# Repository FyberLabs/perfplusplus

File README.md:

# perfplusplus
# Shields and capes that are inspired by https://www.crowdsupply.com/ben-wang/perf-2

Arduino Uno:

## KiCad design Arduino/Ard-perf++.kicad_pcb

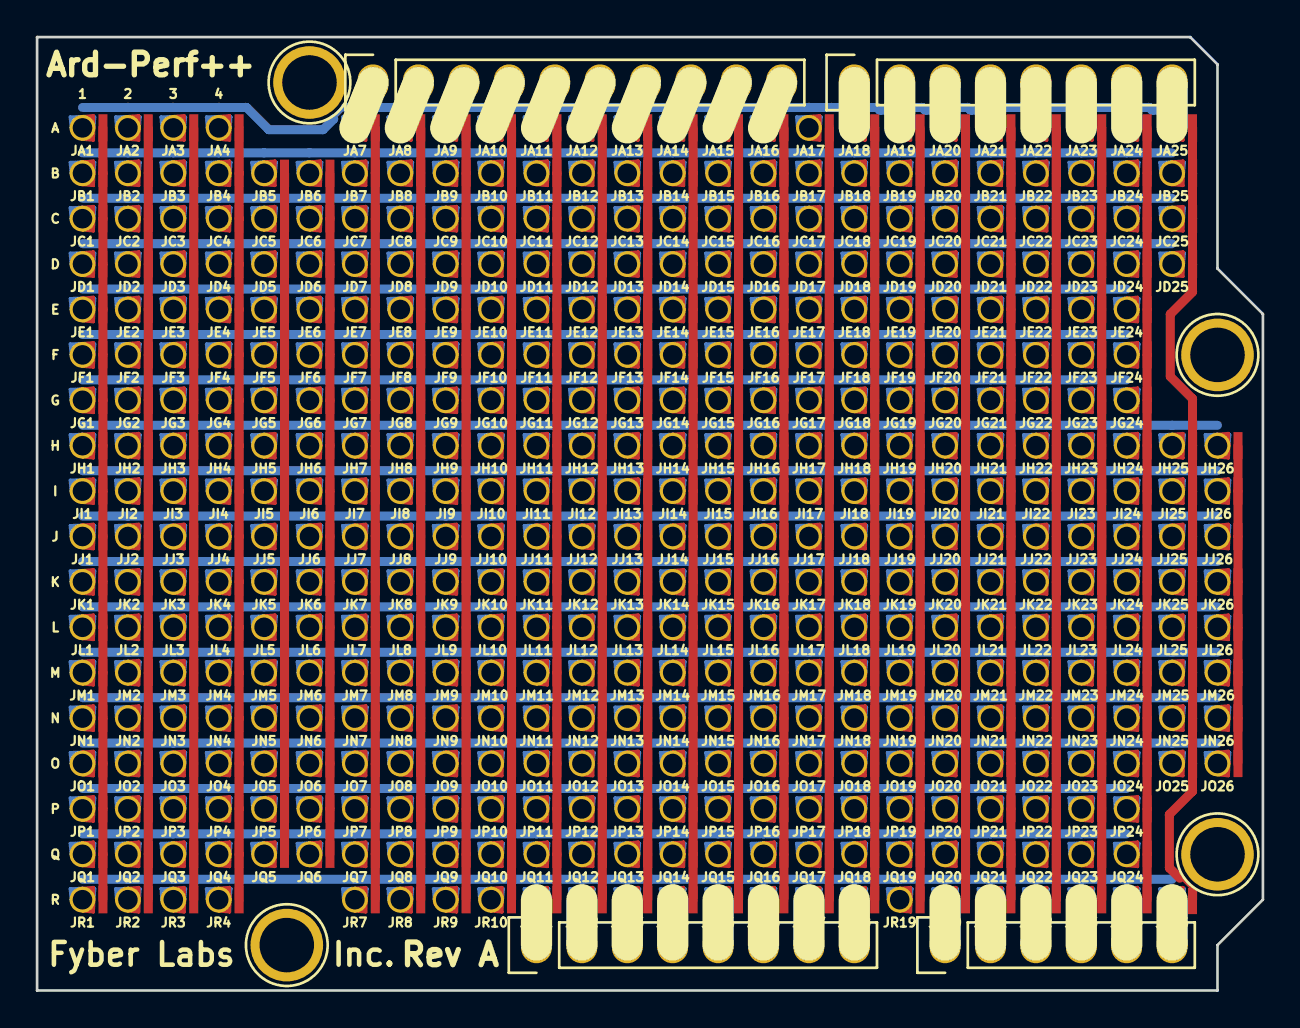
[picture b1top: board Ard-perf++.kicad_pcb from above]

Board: 2 copper layers, 68.6 x 53.3 mm, 457 parts (0 on the bottom side), 76 nets.

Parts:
JA1, JA2, JA3, JA4, JA7, JA8, JA9, JA10, JA11, JA12, JA13, JA14, JA15, JA16, JA17, JA18, JA19, JA20, JA21, JA22, JA23, JA24, JA25: perf+2; 2.54D
JB1, JB2, JB3, JB4, JB5, JB6, JB7, JB8, JB9, JB10, JB11, JB12, JB13, JB14, JB15, JB16, JB17, JB18, JB19, JB20, JB21, JB22, JB23, JB24, JB25: perf+2; 2.54D
JC1, JC2, JC3, JC4, JC5, JC6, JC7, JC8, JC9, JC10, JC11, JC12, JC13, JC14, JC15, JC16, JC17, JC18, JC19, JC20, JC21, JC22, JC23, JC24, JC25: perf+2; 2.54D
JD1, JD2, JD3, JD4, JD5, JD6, JD7, JD8, JD9, JD10, JD11, JD12, JD13, JD14, JD15, JD16, JD17, JD18, JD19, JD20, JD21, JD22, JD23, JD24, JD25: perf+2; 2.54D
JE1, JE2, JE3, JE4, JE5, JE6, JE7, JE8, JE9, JE10, JE11, JE12, JE13, JE14, JE15, JE16, JE17, JE18, JE19, JE20, JE21, JE22, JE23, JE24: perf+2; 2.54D
JF1, JF2, JF3, JF4, JF5, JF6, JF7, JF8, JF9, JF10, JF11, JF12, JF13, JF14, JF15, JF16, JF17, JF18, JF19, JF20, JF21, JF22, JF23, JF24: perf+2; 2.54D
JG1, JG2, JG3, JG4, JG5, JG6, JG7, JG8, JG9, JG10, JG11, JG12, JG13, JG14, JG15, JG16, JG17, JG18, JG19, JG20, JG21, JG22, JG23, JG24: perf+2; 2.54D
JH1, JH2, JH3, JH4, JH5, JH6, JH7, JH8, JH9, JH10, JH11, JH12, JH13, JH14, JH15, JH16, JH17, JH18, JH19, JH20, JH21, JH22, JH23, JH24, JH25, JH26: perf+2; 2.54D
JI1, JI2, JI3, JI4, JI5, JI6, JI7, JI8, JI9, JI10, JI11, JI12, JI13, JI14, JI15, JI16, JI17, JI18, JI19, JI20, JI21, JI22, JI23, JI24, JI25, JI26: perf+2; 2.54D
JJ1, JJ2, JJ3, JJ4, JJ5, JJ6, JJ7, JJ8, JJ9, JJ10, JJ11, JJ12, JJ13, JJ14, JJ15, JJ16, JJ17, JJ18, JJ19, JJ20, JJ21, JJ22, JJ23, JJ24, JJ25, JJ26: perf+2; 2.54D
JK1, JK2, JK3, JK4, JK5, JK6, JK7, JK8, JK9, JK10, JK11, JK12, JK13, JK14, JK15, JK16, JK17, JK18, JK19, JK20, JK21, JK22, JK23, JK24, JK25, JK26: perf+2; 2.54D
JL1, JL2, JL3, JL4, JL5, JL6, JL7, JL8, JL9, JL10, JL11, JL12, JL13, JL14, JL15, JL16, JL17, JL18, JL19, JL20, JL21, JL22, JL23, JL24, JL25, JL26: perf+2; 2.54D
JM1, JM2, JM3, JM4, JM5, JM6, JM7, JM8, JM9, JM10, JM11, JM12, JM13, JM14, JM15, JM16, JM17, JM18, JM19, JM20, JM21, JM22, JM23, JM24, JM25, JM26: perf+2; 2.54D
JN1, JN2, JN3, JN4, JN5, JN6, JN7, JN8, JN9, JN10, JN11, JN12, JN13, JN14, JN15, JN16, JN17, JN18, JN19, JN20, JN21, JN22, JN23, JN24, JN25, JN26: perf+2; 2.54D
JO1, JO2, JO3, JO4, JO5, JO6, JO7, JO8, JO9, JO10, JO11, JO12, JO13, JO14, JO15, JO16, JO17, JO18, JO19, JO20, JO21, JO22, JO23, JO24, JO25, JO26: perf+2; 2.54D
JP1, JP2, JP3, JP4, JP5, JP6, JP7, JP8, JP9, JP10, JP11, JP12, JP13, JP14, JP15, JP16, JP17, JP18, JP19, JP20, JP21, JP22, JP23, JP24: perf+2; 2.54D
JQ1, JQ2, JQ3, JQ4, JQ5, JQ6, JQ7, JQ8, JQ9, JQ10, JQ11, JQ12, JQ13, JQ14, JQ15, JQ16, JQ17, JQ18, JQ19, JQ20, JQ21, JQ22, JQ23, JQ24: perf+2; 2.54D
JR1, JR2, JR3, JR4, JR7, JR8, JR9, JR10, JR11, JR12, JR13, JR14, JR15, JR16, JR17, JR18, JR19, JR20, JR21, JR22, JR23, JR24, JR25: perf+2; 2.54D
P1: Power; Socket_Strip_Arduino_1x08
P2: Analog; Socket_Strip_Arduino_1x06
P3: Digital; Socket_Strip_Arduino_1x10
P4: Digital; Socket_Strip_Arduino_1x08
P5, P6, P7, P8: CONN_01X01; Arduino_1pin

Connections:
+3V3: JR14.1, P1.4
+5V: JR15.1, P1.5
/15x25perf2/JK: JK1.3, JK2.3, JK3.3, JK4.3, JK5.3, JK6.3, JK7.3, JK8.3, JK9.3, JK10.3, JK11.3, JK12.3, JK13.3, JK14.3, JK15.3, JK16.3, JK17.3, JK18.3, JK19.3, JK20.3, JK21.3, JK22.3, JK23.3, JK24.3, JK25.3, JK26.3
/15x25perf2/JL: JL1.3, JL2.3, JL3.3, JL4.3, JL5.3, JL6.3, JL7.3, JL8.3, JL9.3, JL10.3, JL11.3, JL12.3, JL13.3, JL14.3, JL15.3, JL16.3, JL17.3, JL18.3, JL19.3, JL20.3, JL21.3, JL22.3, JL23.3, JL24.3, JL25.3, JL26.3
/15x25perf2/JM: JM1.3, JM2.3, JM3.3, JM4.3, JM5.3, JM6.3, JM7.3, JM8.3, JM9.3, JM10.3, JM11.3, JM12.3, JM13.3, JM14.3, JM15.3, JM16.3, JM17.3, JM18.3, JM19.3, JM20.3, JM21.3, JM22.3, JM23.3, JM24.3, JM25.3, JM26.3
/15x25perf2/JN: JN1.3, JN2.3, JN3.3, JN4.3, JN5.3, JN6.3, JN7.3, JN8.3, JN9.3, JN10.3, JN11.3, JN12.3, JN13.3, JN14.3, JN15.3, JN16.3, JN17.3, JN18.3, JN19.3, JN20.3, JN21.3, JN22.3, JN23.3, JN24.3, JN25.3, JN26.3
/15x25perf2/JO: JO1.3, JO2.3, JO3.3, JO4.3, JO5.3, JO6.3, JO7.3, JO8.3, JO9.3, JO10.3, JO11.3, JO12.3, JO13.3, JO14.3, JO15.3, JO16.3, JO17.3, JO18.3, JO19.3, JO20.3, JO21.3, JO22.3, JO23.3, JO24.3, JO25.3, JO26.3
/15x25perf2/JP: JP1.3, JP2.3, JP3.3, JP4.3, JP5.3, JP6.3, JP7.3, JP8.3, JP9.3, JP10.3, JP11.3, JP12.3, JP13.3, JP14.3, JP15.3, JP16.3, JP17.3, JP18.3, JP19.3, JP20.3, JP21.3, JP22.3, JP23.3, JP24.3
/15x25perf2/JQ: JQ1.3, JQ2.3, JQ3.3, JQ4.3, JQ5.3, JQ6.3, JQ7.3, JQ8.3, JQ9.3, JQ10.3, JQ11.3, JQ12.3, JQ13.3, JQ14.3, JQ15.3, JQ16.3, JQ17.3, JQ18.3, JQ19.3, JQ20.3, JQ21.3, JQ22.3, JQ23.3, JQ24.3
/15x25perf2/JR: JR1.3, JR2.3, JR3.3, JR4.3, JR7.3, JR8.3, JR9.3, JR10.3, JR11.3, JR12.3, JR13.3, JR14.3, JR15.3, JR16.3, JR17.3, JR18.3, JR19.3, JR20.3, JR21.3, JR22.3, JR23.3, JR24.3, JR25.3
/15x25perf2/JR11: JR11.1, P1.1
/15x25perf2/JR12: JR12.1, P1.2
/15x25perf2/JR13: JR13.1, P1.3
/15x25perf2/JR16: JR16.1, P1.6
/15x25perf2/JR17: JR17.1, P1.7
/15x25perf2/JR18: JR18.1, P1.8
/15x25perf2/JR20: JR20.1, P2.1
/15x25perf2/JR21: JR21.1, P2.2
/15x25perf2/JR22: JR22.1, P2.3
/15x25perf2/JR23: JR23.1, P2.4
/15x25perf2/JR24: JR24.1, P2.5
/15x25perf2/JR25: JR25.1, P2.6
/15x25perf/J1: JA1.2, JB1.2, JC1.2, JD1.2, JE1.2, JF1.2, JG1.2, JH1.2, JI1.2, JJ1.2, JK1.2, JL1.2, JM1.2, JN1.2, JO1.2, JP1.2, JQ1.2, JR1.2
/15x25perf/J2: JA2.2, JB2.2, JC2.2, JD2.2, JE2.2, JF2.2, JG2.2, JH2.2, JI2.2, JJ2.2, JK2.2, JL2.2, JM2.2, JN2.2, JO2.2, JP2.2, JQ2.2, JR2.2
/15x25perf/J3: JA3.2, JB3.2, JC3.2, JD3.2, JE3.2, JF3.2, JG3.2, JH3.2, JI3.2, JJ3.2, JK3.2, JL3.2, JM3.2, JN3.2, JO3.2, JP3.2, JQ3.2, JR3.2
/15x25perf/J4: JA4.2, JB4.2, JC4.2, JD4.2, JE4.2, JF4.2, JG4.2, JH4.2, JI4.2, JJ4.2, JK4.2, JL4.2, JM4.2, JN4.2, JO4.2, JP4.2, JQ4.2, JR4.2
/15x25perf/J5: JB5.2, JC5.2, JD5.2, JE5.2, JF5.2, JG5.2, JH5.2, JI5.2, JJ5.2, JK5.2, JL5.2, JM5.2, JN5.2, JO5.2, JP5.2, JQ5.2
/15x25perf/J6: JB6.2, JC6.2, JD6.2, JE6.2, JF6.2, JG6.2, JH6.2, JI6.2, JJ6.2, JK6.2, JL6.2, JM6.2, JN6.2, JO6.2, JP6.2, JQ6.2
/15x25perf/J7: JA7.2, JB7.2, JC7.2, JD7.2, JE7.2, JF7.2, JG7.2, JH7.2, JI7.2, JJ7.2, JK7.2, JL7.2, JM7.2, JN7.2, JO7.2, JP7.2, JQ7.2, JR7.2
/15x25perf/J8: JA8.2, JB8.2, JC8.2, JD8.2, JE8.2, JF8.2, JG8.2, JH8.2, JI8.2, JJ8.2, JK8.2, JL8.2, JM8.2, JN8.2, JO8.2, JP8.2, JQ8.2, JR8.2
/15x25perf/J9: JA9.2, JB9.2, JC9.2, JD9.2, JE9.2, JF9.2, JG9.2, JH9.2, JI9.2, JJ9.2, JK9.2, JL9.2, JM9.2, JN9.2, JO9.2, JP9.2, JQ9.2, JR9.2
/15x25perf/J10: JA10.2, JB10.2, JC10.2, JD10.2, JE10.2, JF10.2, JG10.2, JH10.2, JI10.2, JJ10.2, JK10.2, JL10.2, JM10.2, JN10.2, JO10.2, JP10.2, JQ10.2, JR10.2
/15x25perf/J11: JA11.2, JB11.2, JC11.2, JD11.2, JE11.2, JF11.2, JG11.2, JH11.2, JI11.2, JJ11.2, JK11.2, JL11.2, JM11.2, JN11.2, JO11.2, JP11.2, JQ11.2, JR11.2
/15x25perf/J12: JA12.2, JB12.2, JC12.2, JD12.2, JE12.2, JF12.2, JG12.2, JH12.2, JI12.2, JJ12.2, JK12.2, JL12.2, JM12.2, JN12.2, JO12.2, JP12.2, JQ12.2, JR12.2
/15x25perf/J13: JA13.2, JB13.2, JC13.2, JD13.2, JE13.2, JF13.2, JG13.2, JH13.2, JI13.2, JJ13.2, JK13.2, JL13.2, JM13.2, JN13.2, JO13.2, JP13.2, JQ13.2, JR13.2
/15x25perf/J14: JA14.2, JB14.2, JC14.2, JD14.2, JE14.2, JF14.2, JG14.2, JH14.2, JI14.2, JJ14.2, JK14.2, JL14.2, JM14.2, JN14.2, JO14.2, JP14.2, JQ14.2, JR14.2
/15x25perf/J15: JA15.2, JB15.2, JC15.2, JD15.2, JE15.2, JF15.2, JG15.2, JH15.2, JI15.2, JJ15.2, JK15.2, JL15.2, JM15.2, JN15.2, JO15.2, JP15.2, JQ15.2, JR15.2
/15x25perf/J16: JA16.2, JB16.2, JC16.2, JD16.2, JE16.2, JF16.2, JG16.2, JH16.2, JI16.2, JJ16.2, JK16.2, JL16.2, JM16.2, JN16.2, JO16.2, JP16.2, JQ16.2, JR16.2
/15x25perf/J17: JA17.2, JB17.2, JC17.2, JD17.2, JE17.2, JF17.2, JG17.2, JH17.2, JI17.2, JJ17.2, JK17.2, JL17.2, JM17.2, JN17.2, JO17.2, JP17.2, JQ17.2, JR17.2
/15x25perf/J18: JA18.2, JB18.2, JC18.2, JD18.2, JE18.2, JF18.2, JG18.2, JH18.2, JI18.2, JJ18.2, JK18.2, JL18.2, JM18.2, JN18.2, JO18.2, JP18.2, JQ18.2, JR18.2
/15x25perf/J19: JA19.2, JB19.2, JC19.2, JD19.2, JE19.2, JF19.2, JG19.2, JH19.2, JI19.2, JJ19.2, JK19.2, JL19.2, JM19.2, JN19.2, JO19.2, JP19.2, JQ19.2, JR19.2
/15x25perf/J20: JA20.2, JB20.2, JC20.2, JD20.2, JE20.2, JF20.2, JG20.2, JH20.2, JI20.2, JJ20.2, JK20.2, JL20.2, JM20.2, JN20.2, JO20.2, JP20.2, JQ20.2, JR20.2
/15x25perf/J21: JA21.2, JB21.2, JC21.2, JD21.2, JE21.2, JF21.2, JG21.2, JH21.2, JI21.2, JJ21.2, JK21.2, JL21.2, JM21.2, JN21.2, JO21.2, JP21.2, JQ21.2, JR21.2
/15x25perf/J22: JA22.2, JB22.2, JC22.2, JD22.2, JE22.2, JF22.2, JG22.2, JH22.2, JI22.2, JJ22.2, JK22.2, JL22.2, JM22.2, JN22.2, JO22.2, JP22.2, JQ22.2, JR22.2
/15x25perf/J23: JA23.2, JB23.2, JC23.2, JD23.2, JE23.2, JF23.2, JG23.2, JH23.2, JI23.2, JJ23.2, JK23.2, JL23.2, JM23.2, JN23.2, JO23.2, JP23.2, JQ23.2, JR23.2
/15x25perf/J24: JA24.2, JB24.2, JC24.2, JD24.2, JE24.2, JF24.2, JG24.2, JH24.2, JI24.2, JJ24.2, JK24.2, JL24.2, JM24.2, JN24.2, JO24.2, JP24.2, JQ24.2, JR24.2
/15x25perf/J25: JA25.2, JB25.2, JC25.2, JD25.2, JH25.2, JI25.2, JJ25.2, JK25.2, JL25.2, JM25.2, JN25.2, JO25.2, JR25.2
/15x25perf/J26: JH26.2, JI26.2, JJ26.2, JK26.2, JL26.2, JM26.2, JN26.2, JO26.2
/15x25perf/JA: JA1.3, JA2.3, JA3.3, JA4.3, JA7.3, JA8.3, JA9.3, JA10.3, JA11.3, JA12.3, JA13.3, JA14.3, JA15.3, JA16.3, JA17.3, JA18.3, JA19.3, JA20.3, JA21.3, JA22.3, JA23.3, JA24.3, JA25.3
/15x25perf/JA7: JA7.1, P3.1
/15x25perf/JA8: JA8.1, P3.2
/15x25perf/JA9: JA9.1, P3.3
/15x25perf/JA10: JA10.1, P3.4
/15x25perf/JA11: JA11.1, P3.5
/15x25perf/JA12: JA12.1, P3.6
/15x25perf/JA13: JA13.1, P3.7
/15x25perf/JA14: JA14.1, P3.8
/15x25perf/JA15: JA15.1, P3.9
/15x25perf/JA16: JA16.1, P3.10
/15x25perf/JA18: JA18.1, P4.1
/15x25perf/JA19: JA19.1, P4.2
/15x25perf/JA20: JA20.1, P4.3
/15x25perf/JA21: JA21.1, P4.4
/15x25perf/JA22: JA22.1, P4.5
/15x25perf/JA23: JA23.1, P4.6
/15x25perf/JA24: JA24.1, P4.7
/15x25perf/JA25: JA25.1, P4.8
/15x25perf/JB: JB1.3, JB2.3, JB3.3, JB4.3, JB5.3, JB6.3, JB7.3, JB8.3, JB9.3, JB10.3, JB11.3, JB12.3, JB13.3, JB14.3, JB15.3, JB16.3, JB17.3, JB18.3, JB19.3, JB20.3, JB21.3, JB22.3, JB23.3, JB24.3, JB25.3
/15x25perf/JC: JC1.3, JC2.3, JC3.3, JC4.3, JC5.3, JC6.3, JC7.3, JC8.3, JC9.3, JC10.3, JC11.3, JC12.3, JC13.3, JC14.3, JC15.3, JC16.3, JC17.3, JC18.3, JC19.3, JC20.3, JC21.3, JC22.3, JC23.3, JC24.3, JC25.3
/15x25perf/JD: JD1.3, JD2.3, JD3.3, JD4.3, JD5.3, JD6.3, JD7.3, JD8.3, JD9.3, JD10.3, JD11.3, JD12.3, JD13.3, JD14.3, JD15.3, JD16.3, JD17.3, JD18.3, JD19.3, JD20.3, JD21.3, JD22.3, JD23.3, JD24.3, JD25.3
/15x25perf/JE: JE1.3, JE2.3, JE3.3, JE4.3, JE5.3, JE6.3, JE7.3, JE8.3, JE9.3, JE10.3, JE11.3, JE12.3, JE13.3, JE14.3, JE15.3, JE16.3, JE17.3, JE18.3, JE19.3, JE20.3, JE21.3, JE22.3, JE23.3, JE24.3
/15x25perf/JF: JF1.3, JF2.3, JF3.3, JF4.3, JF5.3, JF6.3, JF7.3, JF8.3, JF9.3, JF10.3, JF11.3, JF12.3, JF13.3, JF14.3, JF15.3, JF16.3, JF17.3, JF18.3, JF19.3, JF20.3, JF21.3, JF22.3, JF23.3, JF24.3
/15x25perf/JG: JG1.3, JG2.3, JG3.3, JG4.3, JG5.3, JG6.3, JG7.3, JG8.3, JG9.3, JG10.3, JG11.3, JG12.3, JG13.3, JG14.3, JG15.3, JG16.3, JG17.3, JG18.3, JG19.3, JG20.3, JG21.3, JG22.3, JG23.3, JG24.3
/15x25perf/JH: JH1.3, JH2.3, JH3.3, JH4.3, JH5.3, JH6.3, JH7.3, JH8.3, JH9.3, JH10.3, JH11.3, JH12.3, JH13.3, JH14.3, JH15.3, JH16.3, JH17.3, JH18.3, JH19.3, JH20.3, JH21.3, JH22.3, JH23.3, JH24.3, JH25.3, JH26.3
/15x25perf/JI: JI1.3, JI2.3, JI3.3, JI4.3, JI5.3, JI6.3, JI7.3, JI8.3, JI9.3, JI10.3, JI11.3, JI12.3, JI13.3, JI14.3, JI15.3, JI16.3, JI17.3, JI18.3, JI19.3, JI20.3, JI21.3, JI22.3, JI23.3, JI24.3, JI25.3, JI26.3
/15x25perf/JJ: JJ1.3, JJ2.3, JJ3.3, JJ4.3, JJ5.3, JJ6.3, JJ7.3, JJ8.3, JJ9.3, JJ10.3, JJ11.3, JJ12.3, JJ13.3, JJ14.3, JJ15.3, JJ16.3, JJ17.3, JJ18.3, JJ19.3, JJ20.3, JJ21.3, JJ22.3, JJ23.3, JJ24.3, JJ25.3, JJ26.3

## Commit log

2017-05-09 updates and name consistency to Ard
2017-05-09 edit tight corner
2017-05-10 fix conflict
2017-05-16 update ard
